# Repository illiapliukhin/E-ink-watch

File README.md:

# E ink watch

Private project: monochrome E Ink wristwatch (KiCad PCB + 3D case).

## Layout
- `kicad/` — schematic, 4-layer PCB, reports
- `case/` — mechanical / IP67 case model and renders

Do not apply VBUS on the dock until power shorts are cleared.

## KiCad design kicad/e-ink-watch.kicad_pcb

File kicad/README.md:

# E Ink Watch — проект KiCad 8/9 (концепт, BLE-only)

Иерархическая схема носимых часов с монохромным E Ink (циферблат + 2 экрана в ремешке).
**NFC отсутствует:** обмен с телефоном и передача тем — только по **BLE** через nRF52840.

> Это **концепт-схема**, не production-ready. Все footprint помечены `TBD`.

## Как открыть в KiCad 8 / 9

1. Установите [KiCad 8](https://www.kicad.org/) или 9.
2. **File → Open Project…** и выберите:
   `/workspace/e-ink-watch-kicad/e-ink-watch.kicad_pro`
   (на Windows после CopyFromBox — путь к скопированной папке).
3. Откроется корневой лист `e-ink-watch.kicad_sch` с иерархическими блоками.
4. Двойной клик по прямоугольнику листа — вход в дочерний sheet.
5. Локальная библиотека символов: `libraries/EInkWatch.kicad_sym` (подключена через `sym-lib-table`).

Генератор (для пересборки): `python3 tools/gen.py`.

## Карта листов

| Файл | Содержание |
|------|------------|
| `e-ink-watch.kicad_sch` | Корень: связи между блоками |
| `power.kicad_sch` | LiPo, BQ25120A, VBAT/VSYS, 3V3, коммутируемый 3V3_DISP |
| `mcu_rf.kicad_sch` | nRF52840 (BLE), кварцы 32 МГц / 32.768 кГц, SPI/I2C/GPIO |
| `displays.kicad_sch` | 3× FPC (MAIN, STRAP_L, STRAP_R), общая SPI, отдельные CS/BUSY |
| `connectors_ui.kicad_sch` | 3 кнопки (BTN1 = pairing), SWD, опц. USB VBUS |

**Нет** `nfc.kicad_sch`, NTAG, катушки LA/LB — по решению дизайна.

## Что разведено (логически)

- **Питание:** разъём LiPo+PCM → BQ25120A → VSYS / 3V3 (always) / 3V3_DISP через P-FET и `DISP_EN`
- **MCU:** nRF52840 (логический pin map, не полный aQFN73) + SWD + SPI0 на 3 E Ink + I2C к PMIC
- **Дисплеи:** общая шина `EPD_SCK`/`EPD_MOSI`/`EPD_DC`/`EPD_RST`, отдельные `CS`×3 и `BUSY`×3
- **UI:** BTN1 / BTN2 / BTN3; **долгий press BTN1 ~3 с** → BLE advertising ~60 с → sleep
- **Кварцы:** HF 32 МГц, LF 32.768 кГц

## Footprints TBD (не готово к производству)

| Ref | Назначение | Footprint |
|-----|------------|-----------|
| U1 | BQ25120A | `TBD:BQ25120A_DSBGA` |
| U2 | nRF52840 / модуль | `TBD:nRF52840_QIAA_or_MDBT50Q` |
| J1 | LiPo | `TBD:JST_PH_2pin` |
| J2–J4 | FPC E Ink | `TBD:ZIF_0.5mm_10pin` |
| J5 | SWD | `TBD:TagConnect_or_1x04` |
| J6 | USB VBUS | `TBD:USB_C_or_pogo` |
| SW1–3 | кнопки | `TBD:tactile_side` |
| Y1/Y2 | кварцы | `TBD:HF_XTAL` / `TBD:ABS07` |
| Q1 | load switch | `TBD:SOT23` |
| пассивы | R/C/FB | `TBD:0402` / `0603` |

Символ nRF52840 — **логический wearable map**, не полный pinout корпуса. Перед разводкой сверить с QIAA/CKAA / datasheet модуля.

## Документы

Копии исходного engineering package: каталог `docs/` (README, ARCHITECTURE, BOM, SCHEMATIC_BLOCKS, PCB_GUIDELINES).  
Учтите: исходные docs ещё упоминают NFC — для железа этого KiCad-проекта NFC **снят**; актуальные решения — в `DESIGN_NOTES.md`.

## PCB REV0.1 (placement + route)

На `e-ink-watch.kicad_pcb` выполнены **fine placement** внутри Ø40 мм (U1 сверху-центр, U2 под ним, развязка C1–C4/R1–R2 рядом, FPC MAIN/L/R на 12/9/3 ч, J_BAT на 6 ч, SW1–3 по нижней-правой дуге, J_SWD слева-снизу) и **черновая разводка** питания (VBAT/VSYS/3V3/3V3_DISP/GND, зона GND на B.Cu и 3V3 на F.Cu) плюс SPI к трём FPC (`EPD_SCK`/`MOSI`/`DC`/`RST`/`CS_*`/`BUSY_*`, 0.18 мм сигнал / 0.4–0.5 мм питание). Генератор: `tools/gen_pcb.py`; допущения pin-map — `tools/ROUTE_NOTES.md`; превью — `docs/pcb_routed.svg`.
## Статус

Концепт, сентябрь 2026. Rev `0.2-concept-ble` + PCB **REV0.1** (placed+routed).

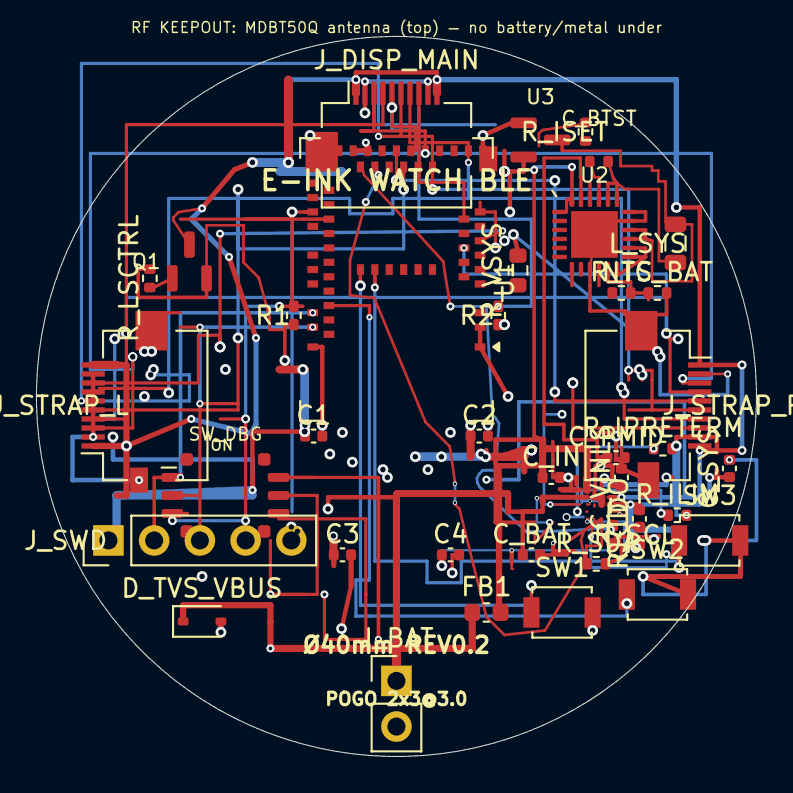
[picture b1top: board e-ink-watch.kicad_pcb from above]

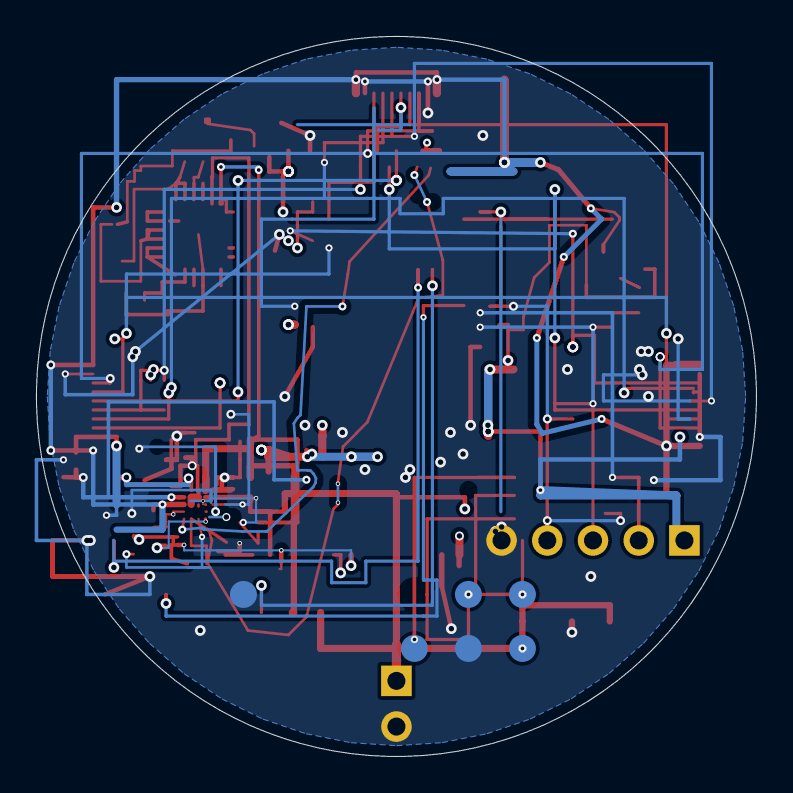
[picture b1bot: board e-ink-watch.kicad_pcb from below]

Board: 4 copper layers, 40.0 x 40.0 mm, 45 parts (6 on the bottom side), 36 nets.

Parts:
C1, C2: 100n; C_0402_1005Metric
C3, C4: 10u; C_0402_1005Metric
C_BAT: 1uF; C_0402_1005Metric
C_BTST: 47nF; R_0402_1005Metric
C_IN: 1uF; C_0402_1005Metric
C_LDO: 1uF; C_0402_1005Metric
C_PMID: 4.7uF; C_0402_1005Metric
C_SYS: 10uF; C_0402_1005Metric
C_VINLS: 1uF; C_0402_1005Metric
D_TVS_VBUS: PESD5V0S1U; D_SOD-323
FB1: BLM18PG121SN1; L_0603_1608Metric
J_BAT: BAT; PinHeader_1x02_P2.54mm_Vertical
J_DISP_MAIN: DISP_MAIN; Hirose_FH12-10S-0.5SH_1x10-1MP_P0.50mm_Horizontal
J_STRAP_L: STRAP_L; Hirose_FH12-10S-0.5SH_1x10-1MP_P0.50mm_Horizontal
J_STRAP_R: STRAP_R; Hirose_FH12-10S-0.5SH_1x10-1MP_P0.50mm_Horizontal
J_SWD: SWD; PinHeader_1x05_P2.54mm_Vertical
L_SYS: 2.2uH; L_0805_2012Metric
NTC_BAT: 10k_NTC; R_0402_1005Metric
Q1: DMG2305UX; SOT-23
R1, R2: 10k; R_0402_1005Metric
R_CD: 10k; R_0402_1005Metric
R_ILIM: 2.0k; R_0402_1005Metric
R_IPRETERM: 0R; R_0402_1005Metric
R_ISET: 10k; R_0402_1005Metric
R_LSCTRL: 100k; R_0402_1005Metric
R_SCL: 4.7k; R_0402_1005Metric
R_SDA: 4.7k; R_0402_1005Metric
R_TS: 5.1k; R_0402_1005Metric
R_VSYS: 4.7uF; R_0603_1608Metric
SW1: BTN1; SW_SPST_B3U-1000P
SW2: BTN2; SW_SPST_B3U-1000P
SW3: BTN3; SW_SPST_B3U-1000P
SW_DBG: PROG EN; SW_DIP_SPSTx03_Slide_Copal_CVS-03xB_W5.9mm_P1mm
TP1: VCHG; Pogo_Pad_D1.5mm
TP2: GND; Pogo_Pad_D1.5mm
TP3: SWDIO; Pogo_Pad_D1.5mm
TP4: SWDCLK; Pogo_Pad_D1.5mm
TP5: nRESET; Pogo_Pad_D1.5mm
TP6: OPT; Pogo_Pad_D1.5mm
U1: MDBT50Q-1MV2; Raytac_MDBT50Q
U2: BQ25619; BQ25619_RTW_WQFN-24_4x4mm_P0.5mm
U3: MCP1700-3302; SOT-23

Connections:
3V3: C1.1, C2.1, C3.1, C4.1, J_SWD.1, Q1.2, R1.1, R2.1, R_LSCTRL.2, R_SCL.2, R_SDA.2, U1.28, U1.30, U3.2
3V3_DISP: C_LDO.2, J_DISP_MAIN.1, J_DISP_MAIN.10, J_STRAP_L.1, J_STRAP_L.10, J_STRAP_R.1, J_STRAP_R.10, Q1.3
BTN1: SW1.1, U1.61
BTN2: SW2.1, U1.50
BTN3: SW3.1, U1.60
BTST: C_BTST.1, U2.21
DISP_EN: Q1.1, R_LSCTRL.1
EPD_BUSY_L: J_STRAP_L.8, U1.10
EPD_BUSY_MAIN: J_DISP_MAIN.8, U1.13
EPD_BUSY_R: J_STRAP_R.8, U1.14
EPD_CS_L: J_STRAP_L.5, U1.23
EPD_CS_MAIN: J_DISP_MAIN.5, R2.2, U1.22
EPD_CS_R: J_STRAP_R.5, U1.24
EPD_DC: J_DISP_MAIN.6, J_STRAP_L.6, J_STRAP_R.6, U1.19
EPD_MOSI: J_DISP_MAIN.3, J_STRAP_L.3, J_STRAP_R.3, U1.20
EPD_RST: J_DISP_MAIN.7, J_STRAP_L.7, J_STRAP_R.7, U1.16
EPD_SCK: J_DISP_MAIN.4, J_STRAP_L.4, J_STRAP_R.4, U1.9
GND: C1.2, C2.2, C3.2, C4.2, C_BAT.2, C_IN.2, C_LDO.1, C_PMID.2, C_SYS.2, C_VINLS.2, D_TVS_VBUS.2, J_BAT.2, J_DISP_MAIN.2, J_DISP_MAIN.9, J_DISP_MAIN.MP, J_STRAP_L.2, J_STRAP_L.9, J_STRAP_L.MP, J_STRAP_R.2, J_STRAP_R.9, J_STRAP_R.MP, J_SWD.5, NTC_BAT.2, R_CD.2, R_ILIM.2, R_IPRETERM.2, R_VSYS.2, SW1.2, SW2.2, SW3.2, TP2.1, U1.1, U1.2, U1.15, U1.33, U1.55, U2.9, U2.17, U2.18, U2.25, U3.1
PMIC_INT: U1.39, U2.7
PMID: C_PMID.1, C_VINLS.1, U2.23
PSEL: R_ISET.2, U2.2
REGN: R_ISET.1, R_TS.1, R_VSYS.1, U2.22
SCL: R_SCL.1, U1.29, U2.5
SDA: R_SDA.1, U1.27, U2.6
SW: C_BTST.2, L_SYS.1, U2.19, U2.20
SWDCLK: J_SWD.3, SW_DBG.2, U1.53
SWDCLK_POGO: SW_DBG.5, TP4.1
SWDIO: J_SWD.2, SW_DBG.1, U1.51
SWDIO_POGO: SW_DBG.6, TP3.1
TS: NTC_BAT.1, R_TS.2, U2.11
VBAT: C_BAT.1, J_BAT.1, U2.10, U2.12, U2.13, U2.14
VBUS: C_IN.1, FB1.2, U2.1, U2.24
VBUS_POGO: D_TVS_VBUS.1, FB1.1, TP1.1
VSYS: C_SYS.1, L_SYS.2, U2.15, U2.16, U3.3
nRESET: J_SWD.4, R1.2, SW_DBG.3, U1.40
nRESET_POGO: SW_DBG.4, TP5.1
